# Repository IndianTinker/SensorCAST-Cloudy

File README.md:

SensorCAST-Cloudy
=================

The Web Connected Weather Logger based on GR-Sakura Board.
Contains the corel draw file for laser cutting the enclosure
Contains the C code and all the required board layouts and schematics

For any queries you can email me at indiantinker[at]gmail[dot]com

The working project video is :
http://www.youtube.com/watch?v=amBn-kbNLqY

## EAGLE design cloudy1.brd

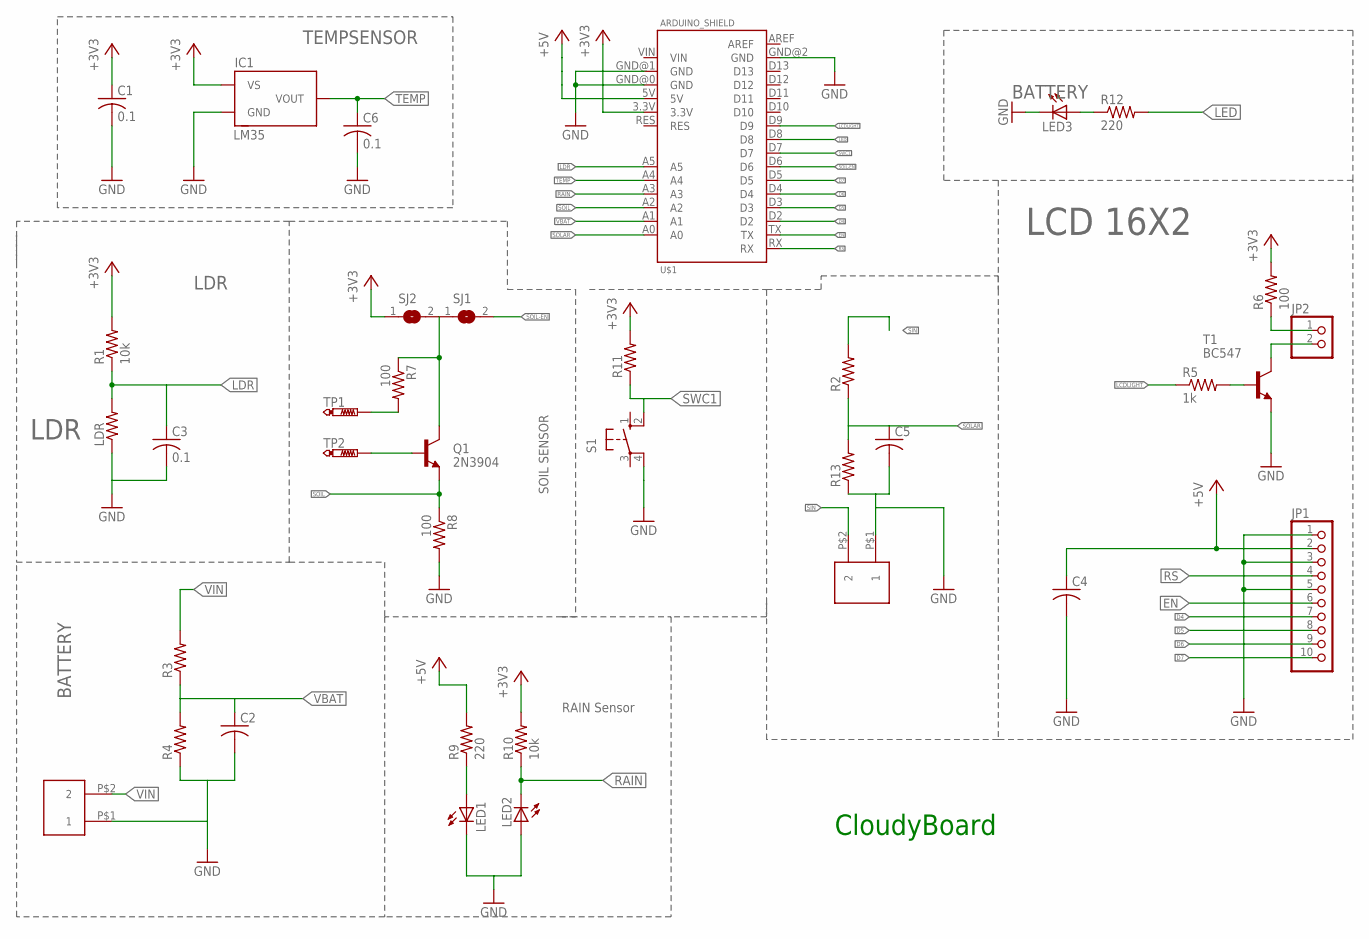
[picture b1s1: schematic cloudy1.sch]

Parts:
C1, C3, C6: 0.1; C0805
C2, C4, C5: C-USC0805; C0805
IC1: LM35; TO92
JP1: PINHD-1X10; 1X10
JP2: PINHD-1X2; 1X02
LDR: R-US_0204/5; 0204/5
LED1, LED2, LED3: LED5MM
Q1: 2N3904; TO92
R1, R10: 10k; 0204/7
R2, R3, R4, R13: R-US_0204/7; 0204/7
R5: 1k; 0204/7
R6: 100; 0204/7
R7, R8: 100; R0805
R9, R12: 220; 0204/7
R11: R-US_0207/10; 0207/10
S1: 10-XX; B3F-10XX
SJ1, SJ2: SJ
T1: BC547; TO92
TP1, TP2: PTR1TP19SQ; TP19SQ
U$1: ARDUINO_SHIELD
U$2, U$3: POWER_TERMINAL; POWER_TERMINAL_2

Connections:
+3V3: C1.1, IC1.VS, R1.2, R6.2, R10.2, R11.2, SJ2.1, U$1.3.3V
+5V: C4.1, JP1.2, R9.2, U$1.5V
D4: JP1.7, U$1.D2
D5: JP1.8, U$1.D3
D6: JP1.9, U$1.D4
D7: JP1.10, U$1.D5
EN: JP1.6, U$1.TX
GND: C1.2, C2.2, C3.2, C4.2, C5.2, C6.2, IC1.GND, JP1.1, JP1.3, JP1.5, LDR.1, LED1.K (C), LED2.A, LED3.K (C), R4.1, R8.2, R13.1, S1.4 (P1), T1.1 (E), U$1.GND@0 (GND), U$1.GND@1 (GND), U$1.GND@2 (GND), U$2.P$1 (1), U$3.P$1 (1)
LCDLIGHT: R5.1, U$1.D9
LDR: C3.1, LDR.2, R1.1, U$1.A5
LED: R12.2, U$1.D8
unnamed: JP2.1, R6.1
unnamed: JP2.2, T1.3 (C)
unnamed: R5.2, T1.2 (B)
unnamed: Q1.2 (B), TP2.TP
unnamed: R7.2, TP1.TP
unnamed: Q1.1 (C), R7.1, SJ1.1, SJ2.2
unnamed: LED1.A, R9.1
unnamed: LED3.A, R12.1
RAIN: LED2.K (C), R10.1, U$1.A3
RS: JP1.4, U$1.RX
SIN: R2.2, U$3.P$2 (2)
SOIL: Q1.3 (E), R8.1, U$1.A2
SOIL-EN: SJ1.2, U$1.D6
SOLAR: C5.1, R2.1, R13.2, U$1.A0
SWC1: R11.1, S1.2 (S1), U$1.D7
TEMP: C6.1, IC1.VOUT, U$1.A4
VBAT: C2.1, R3.1, R4.2, U$1.A1
VIN: R3.2, U$2.P$2 (2)

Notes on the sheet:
LDR
LCD 16X2
TEMPSENSOR
BATTERY
SOIL SENSOR
RAIN Sensor
CloudyBoard

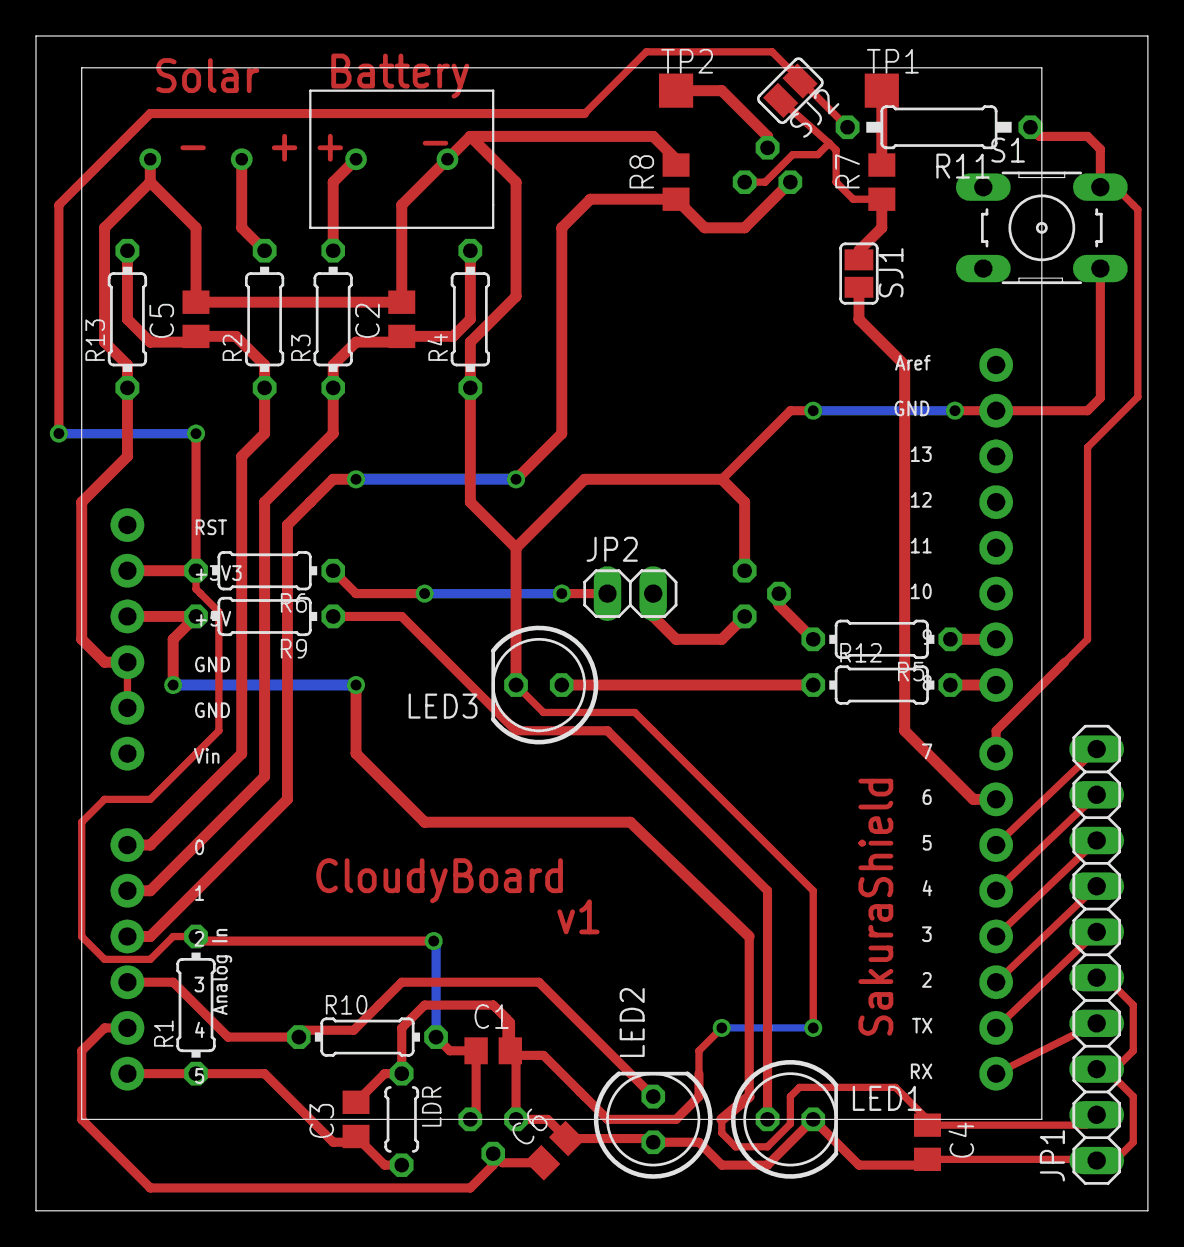
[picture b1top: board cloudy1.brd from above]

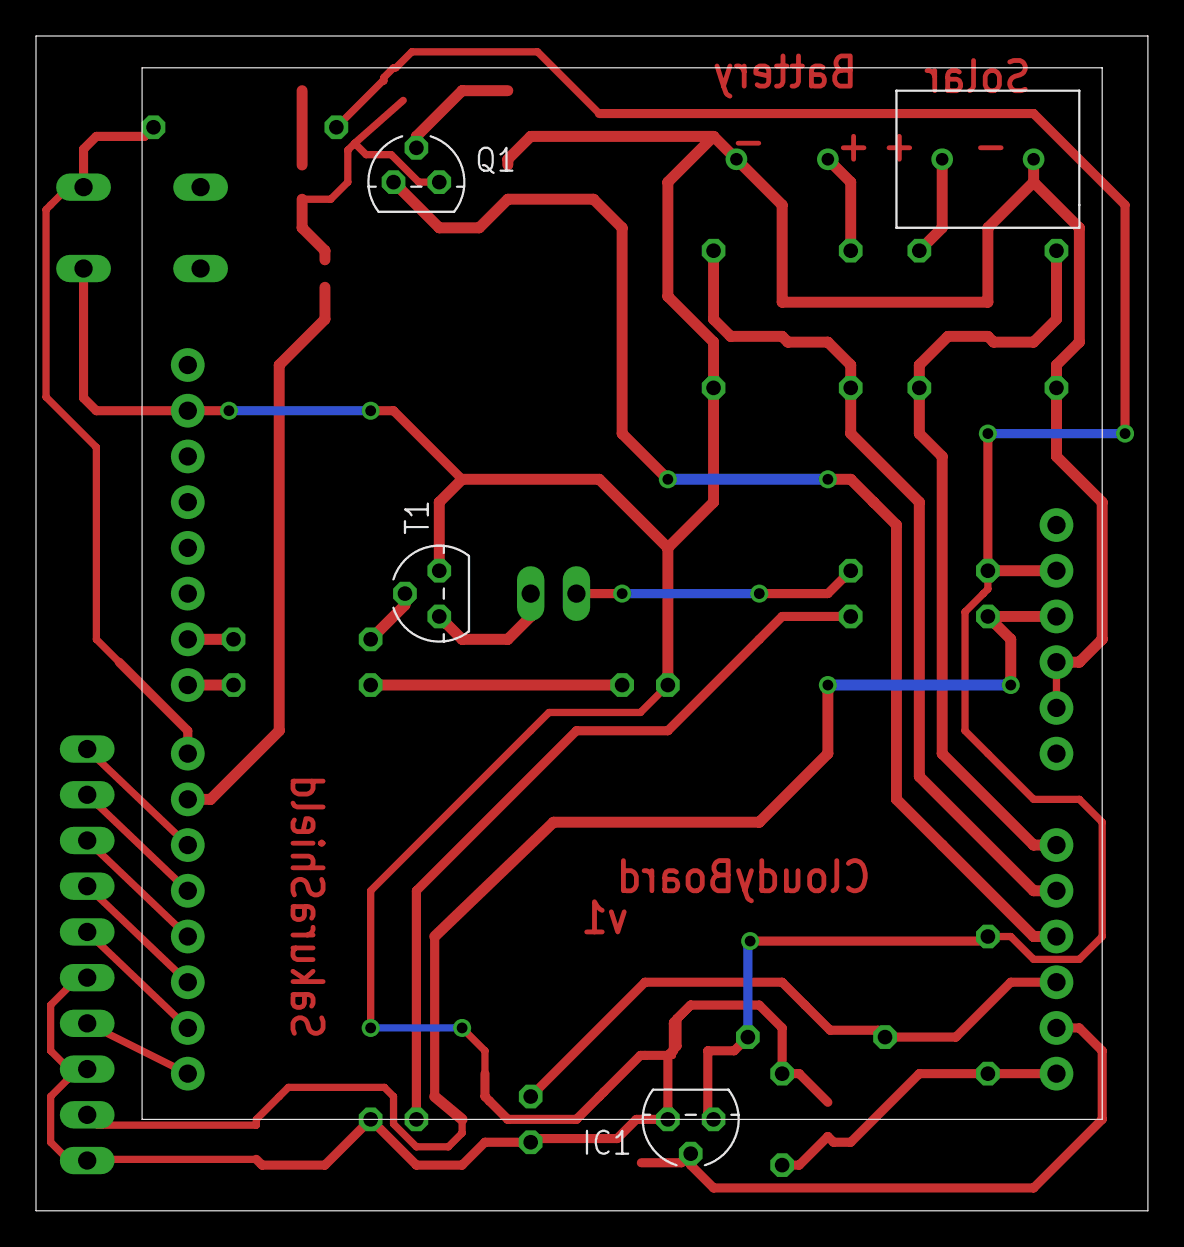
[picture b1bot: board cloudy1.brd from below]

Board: 2 copper layers, 61.8 x 65.3 mm, 36 parts (4 on the bottom side), 29 nets.

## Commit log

2013-12-02 Added Files
    All files were added
